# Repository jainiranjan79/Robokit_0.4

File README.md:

# scratchduino-RoboKit v0.4
This repository includes **body, schematics, PCB, documentation and sources** for RoboKit v0.4

#Directories
* Body - *the body of roboplatform and sensors*
* Documentation - *the .pdf schematics, etc*
* Firmware - *the firmware for RoboKit v0.4*
* PCB - *Printed Circuit Boards for Roboplatform and sensors*
    * Gerber - *gerber files + gerber drill files*
        * Cartridge
        * ...
    * SVG - *svg files without drill files*
        * Cartridge
        * ...
* Sources - *the sources for PCB and Body*
    * Cartridge - *Kicad files for PCB*
        * make - *This bash script distribute Gerber, SVG and PDF files to directories PCB,Documentation*
        * PCB - *Here you need print PCB in svg and gerber formats( read make )*
    * ...

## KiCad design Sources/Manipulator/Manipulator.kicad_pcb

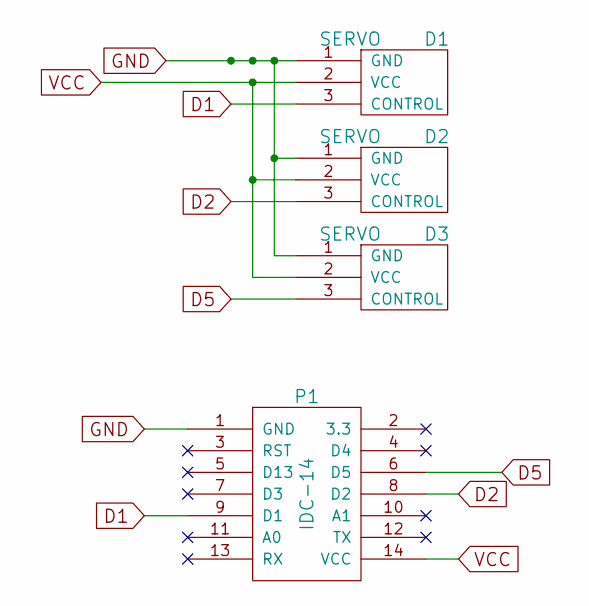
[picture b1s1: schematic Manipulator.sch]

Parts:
D1, D2, D3: SERVO
P1: IDC-14

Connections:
D1: D1.3 (CONTROL), P1.9 (D1)
D2: D2.3 (CONTROL), P1.8 (D2)
D5: D3.3 (CONTROL), P1.6 (D5)
GND: D1.1 (GND), D2.1 (GND), D3.1 (GND), P1.1 (GND)
VCC: D1.2 (VCC), D2.2 (VCC), D3.2 (VCC), P1.14 (VCC)

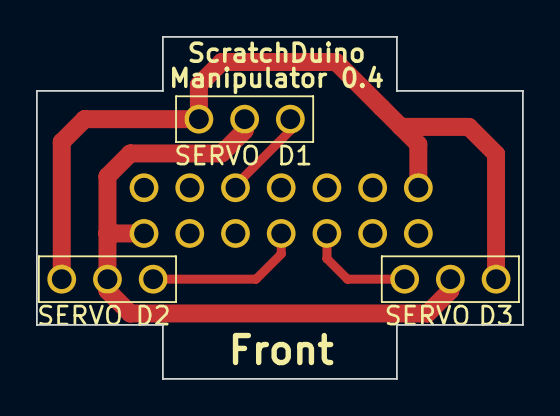
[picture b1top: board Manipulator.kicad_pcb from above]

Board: 2 copper layers, 27.0 x 19.0 mm, 4 parts (1 on the bottom side), 5 nets.

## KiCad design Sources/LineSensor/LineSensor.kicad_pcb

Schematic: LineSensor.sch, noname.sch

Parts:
D1: INFAREDPHOTODIODE
D2: INFAREDLED
P1: SENSOR
R1: 100
R3: 100K

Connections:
unnamed: D1.1, P1.4 (A), R3.1
unnamed: D1.2, P1.2 (VCC), R1.1
unnamed: D2.2, P1.1 (GND), R3.2
unnamed: D2.1, R1.2

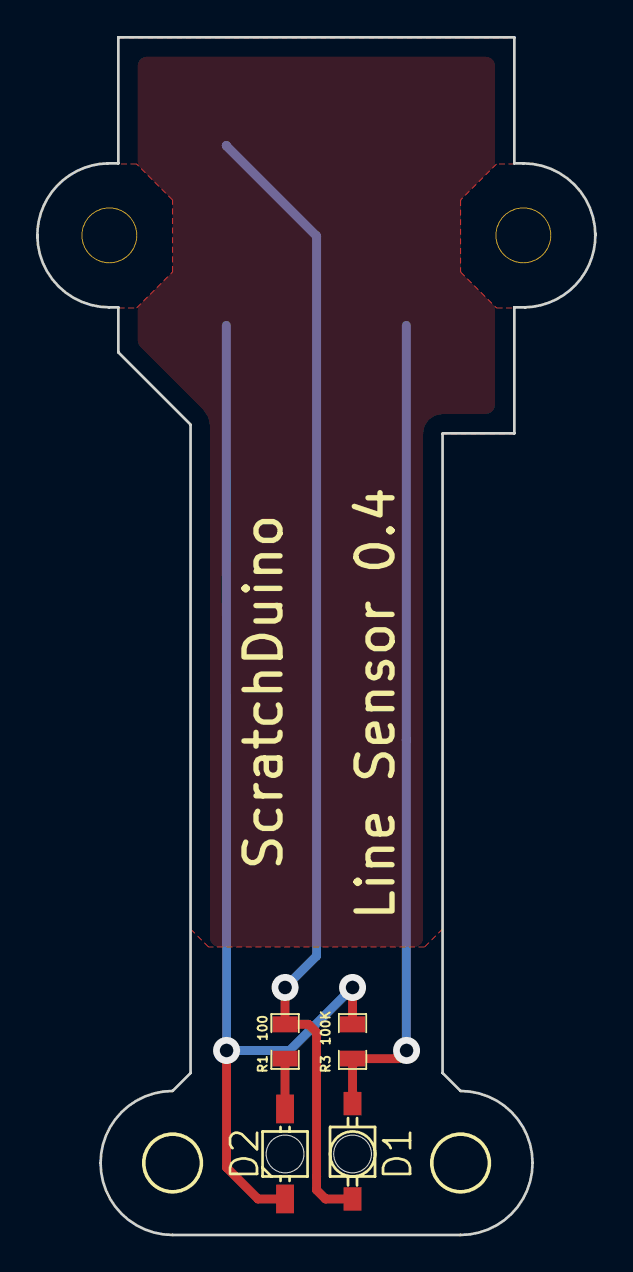
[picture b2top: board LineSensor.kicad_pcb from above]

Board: 2 copper layers, 31.0 x 66.5 mm, 5 parts (1 on the bottom side), 4 nets.

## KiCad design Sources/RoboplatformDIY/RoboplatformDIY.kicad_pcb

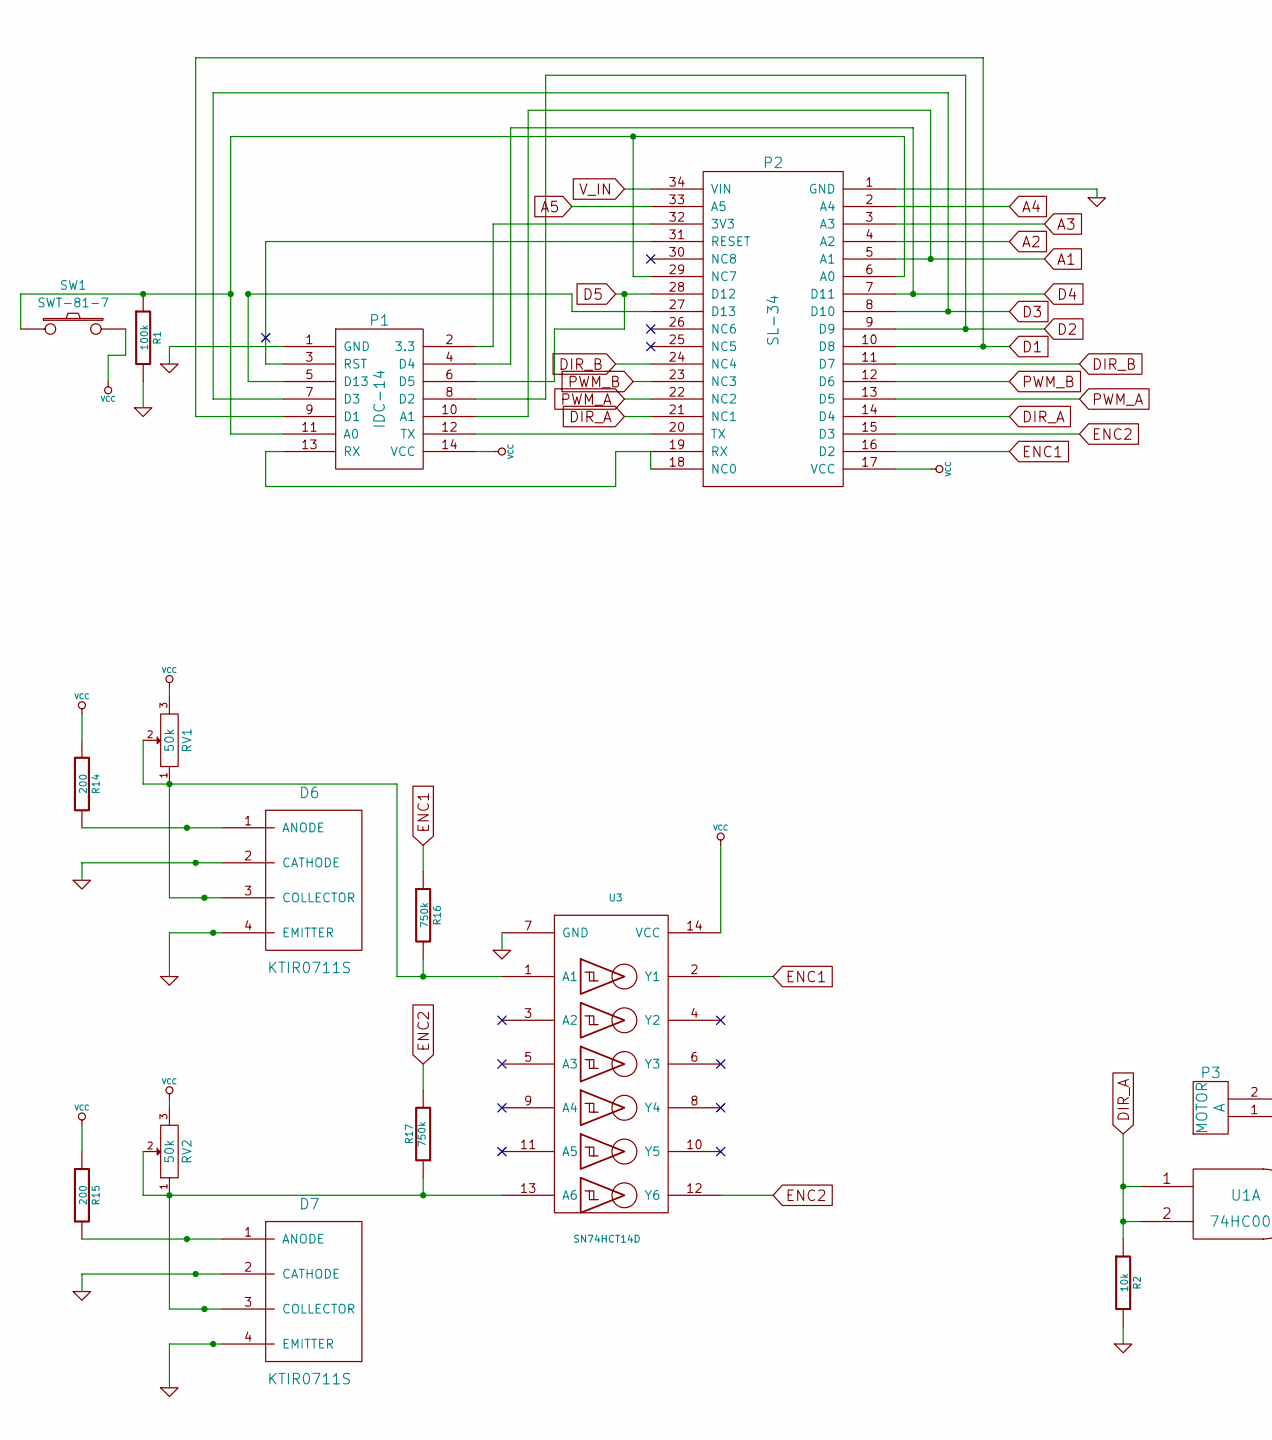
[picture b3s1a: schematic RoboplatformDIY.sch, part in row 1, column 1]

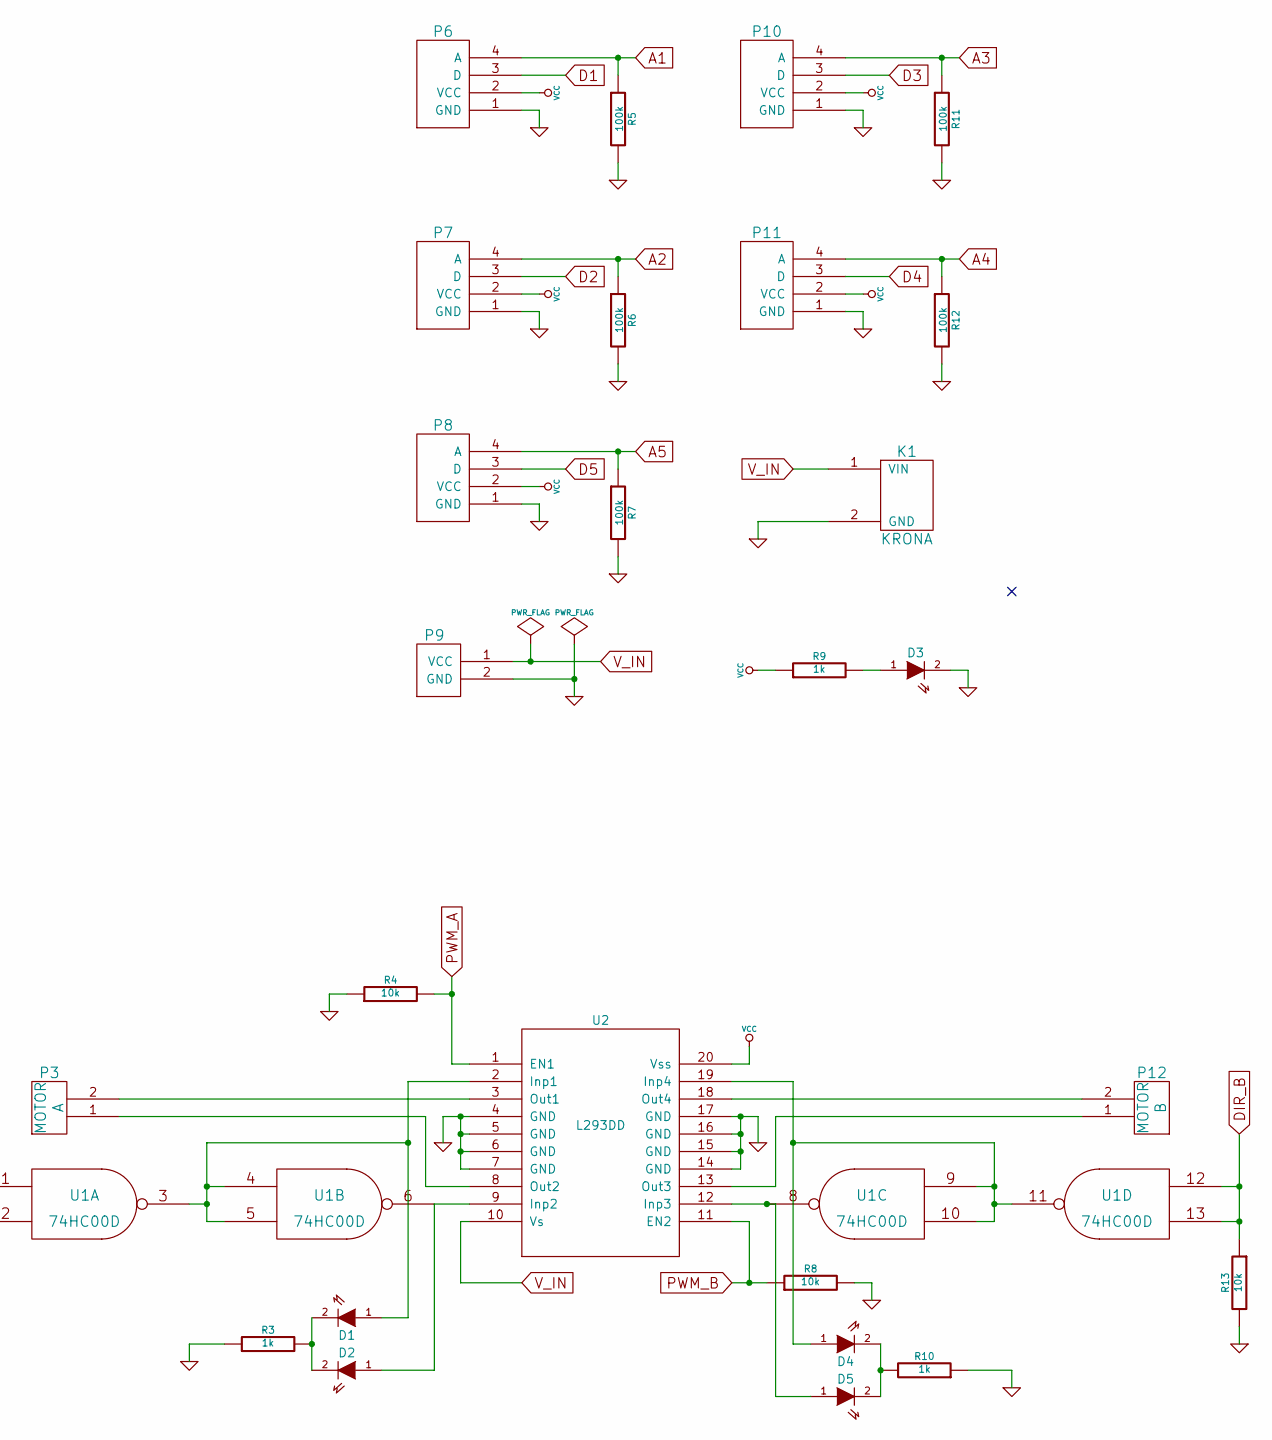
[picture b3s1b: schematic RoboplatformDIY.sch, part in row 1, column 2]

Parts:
D1, D2, D3, D4, D5: LED
D6, D7: KTIR0711S
K1: KRONA
P1: IDC-14
P2: SL-34
P3, P12: MOTOR
P6, P7, P8, P10: SENSOR
P9: POWER
P11: SENSOR
R1, R5, R6, R7, R11, R12: 100k
R2, R4, R8, R13: 10k
R3, R9, R10: 1k
R14, R15: 200
R16, R17: 750k
RV1, RV2: 50k
SW1: SWT-81-7
U1: 74HC00D
U2: L293DD; MODULE
U3: SN74HCT14D

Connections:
A1: P1.10 (A1), P2.5 (A1), P6.4 (A), R5.1
A2: P2.4 (A2), P7.4 (A), R6.1
A3: P2.3 (A3), P10.4 (A), R11.1
A4: P2.2 (A4), P11.4 (A), R12.1
A5: P2.33 (A5), P8.4 (A), R7.1
D1: P1.9 (D1), P2.10 (D8), P6.3 (D)
D2: P1.8 (D2), P2.9 (D9), P7.3 (D)
D3: P1.7 (D3), P2.8 (D10), P10.3 (D)
D4: P1.4 (D4), P2.7 (D11), P11.3 (D)
D5: P1.6 (D5), P2.28 (D12), P8.3 (D)
DIR_A: P2.14 (D4), P2.21 (NC1), R2.1, U1.1, U1.2
DIR_B: P2.11 (D7), P2.24 (NC4), R13.1, U1.12, U1.13
ENC1: P2.16 (D2), R16.1, U3.2 (Y1)
ENC2: P2.15 (D3), R17.2, U3.12 (Y6)
GND: D3.2 (K), D6.2 (CATHODE), D6.4 (EMITTER), D7.2 (CATHODE), D7.4 (EMITTER), K1.2 (GND), P1.1 (GND), P2.1 (GND), P6.1 (GND), P7.1 (GND), P8.1 (GND), P9.2 (GND), P10.1 (GND), P11.1 (GND), R1.2, R2.2, R3.1, R4.1, R5.2, R6.2, R7.2, R8.2, R10.1, R11.2, R12.2, R13.2, U1.7 (GND), U2.4 (GND), U2.5 (GND), U2.6 (GND), U2.7 (GND), U2.14 (GND), U2.15 (GND), U2.16 (GND), U2.17 (GND), U3.7 (GND)
unnamed: P1.12 (TX), P2.20 (TX)
unnamed: P1.13 (RX), P2.18 (NC0), P2.19 (RX)
unnamed: P1.3 (RST), P2.31 (RESET)
unnamed: P1.2 (3.3), P2.32 (3V3)
unnamed: P3.2, U2.3 (Out1)
unnamed: P1.11 (A0), P2.6 (A0), P2.29 (NC7), R1.1, SW1.1
unnamed: P3.1, U2.8 (Out2)
unnamed: D1.1 (A), U1.3, U1.4, U1.5, U2.2 (Inp1)
unnamed: P12.1, U2.13 (Out3)
unnamed: P12.2, U2.18 (Out4)
unnamed: D4.1 (A), U1.9, U1.10, U1.11, U2.19 (Inp4)
unnamed: D7.1 (ANODE), R15.2
unnamed: D6.1 (ANODE), R14.2
unnamed: D2.1 (A), U1.6, U2.9 (Inp2)
unnamed: P1.5 (D13), P2.27 (D13)
unnamed: D3.1 (A), R9.2
unnamed: D7.3 (COLLECTOR), R17.1, RV2.1, RV2.2, U3.13 (A6)
unnamed: D6.3 (COLLECTOR), R16.2, RV1.1, RV1.2, U3.1 (A1)
unnamed: D1.2 (K), D2.2 (K), R3.2
unnamed: D4.2 (K), D5.2 (K), R10.2
unnamed: D5.1 (A), U1.8, U2.12 (Inp3)
PWM_A: P2.13 (D5), P2.22 (NC2), R4.2, U2.1 (EN1)
PWM_B: P2.12 (D6), P2.23 (NC3), R8.1, U2.11 (EN2)
VCC: P1.14 (VCC), P2.17 (VCC), P6.2 (VCC), P7.2 (VCC), P8.2 (VCC), P10.2 (VCC), P11.2 (VCC), R9.1, R14.1, R15.1, RV1.3, RV2.3, SW1.2, U1.14 (VCC), U2.20 (Vss), U3.14 (VCC)
V_IN: K1.1 (VIN), P2.34 (VIN), P9.1 (VCC), U2.10 (Vs)

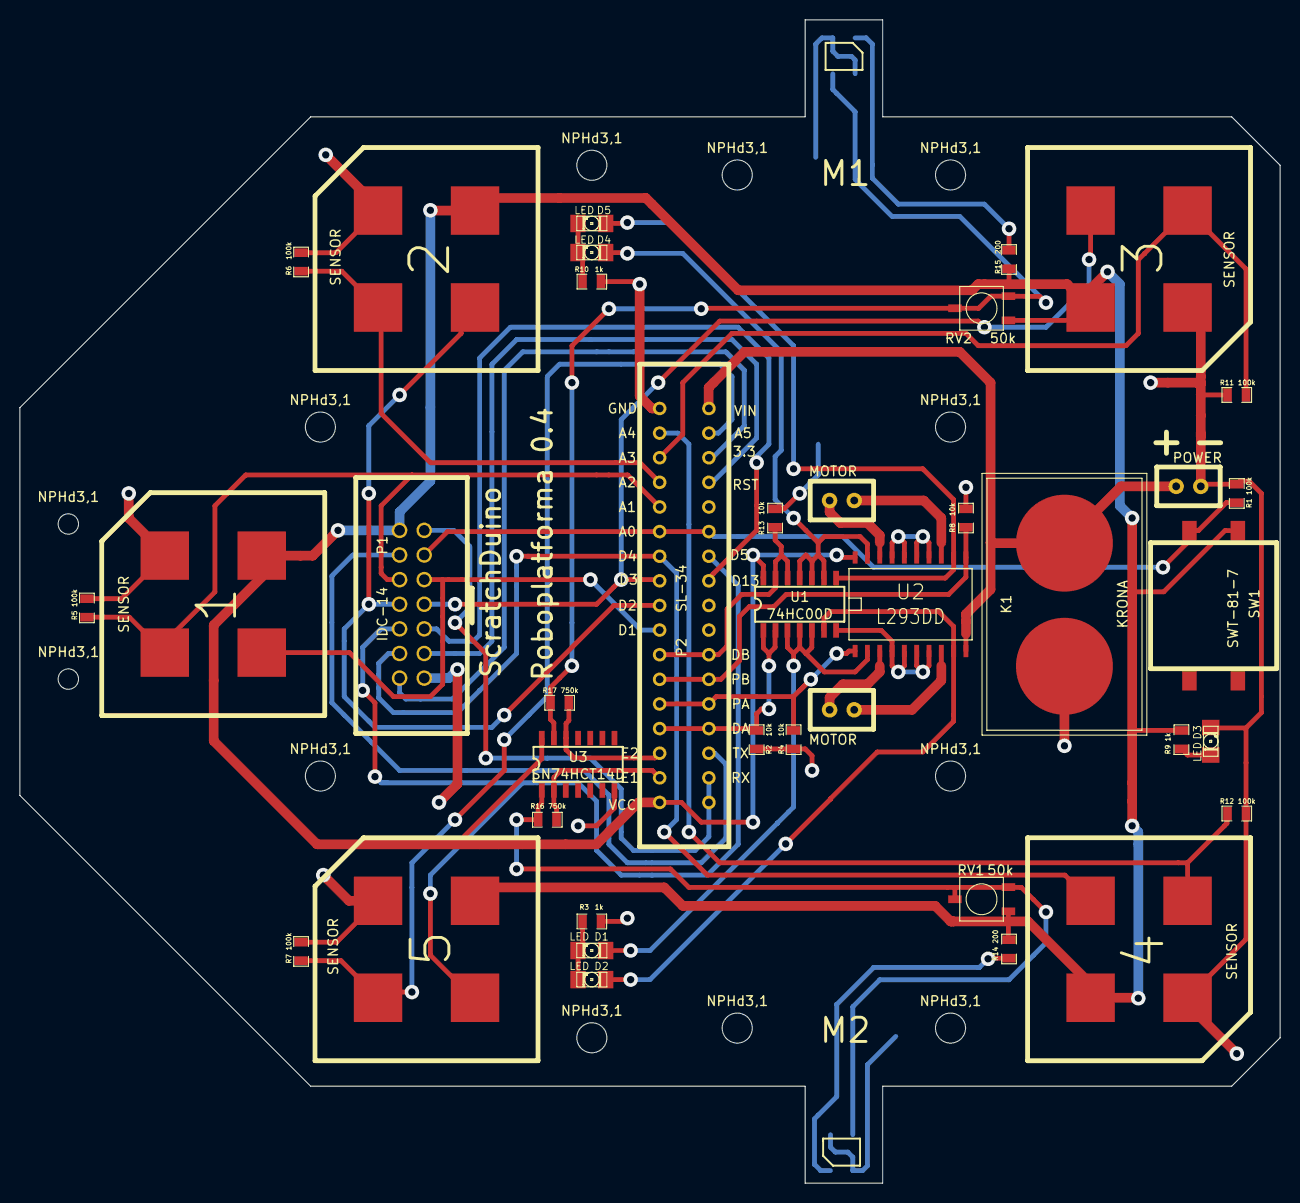
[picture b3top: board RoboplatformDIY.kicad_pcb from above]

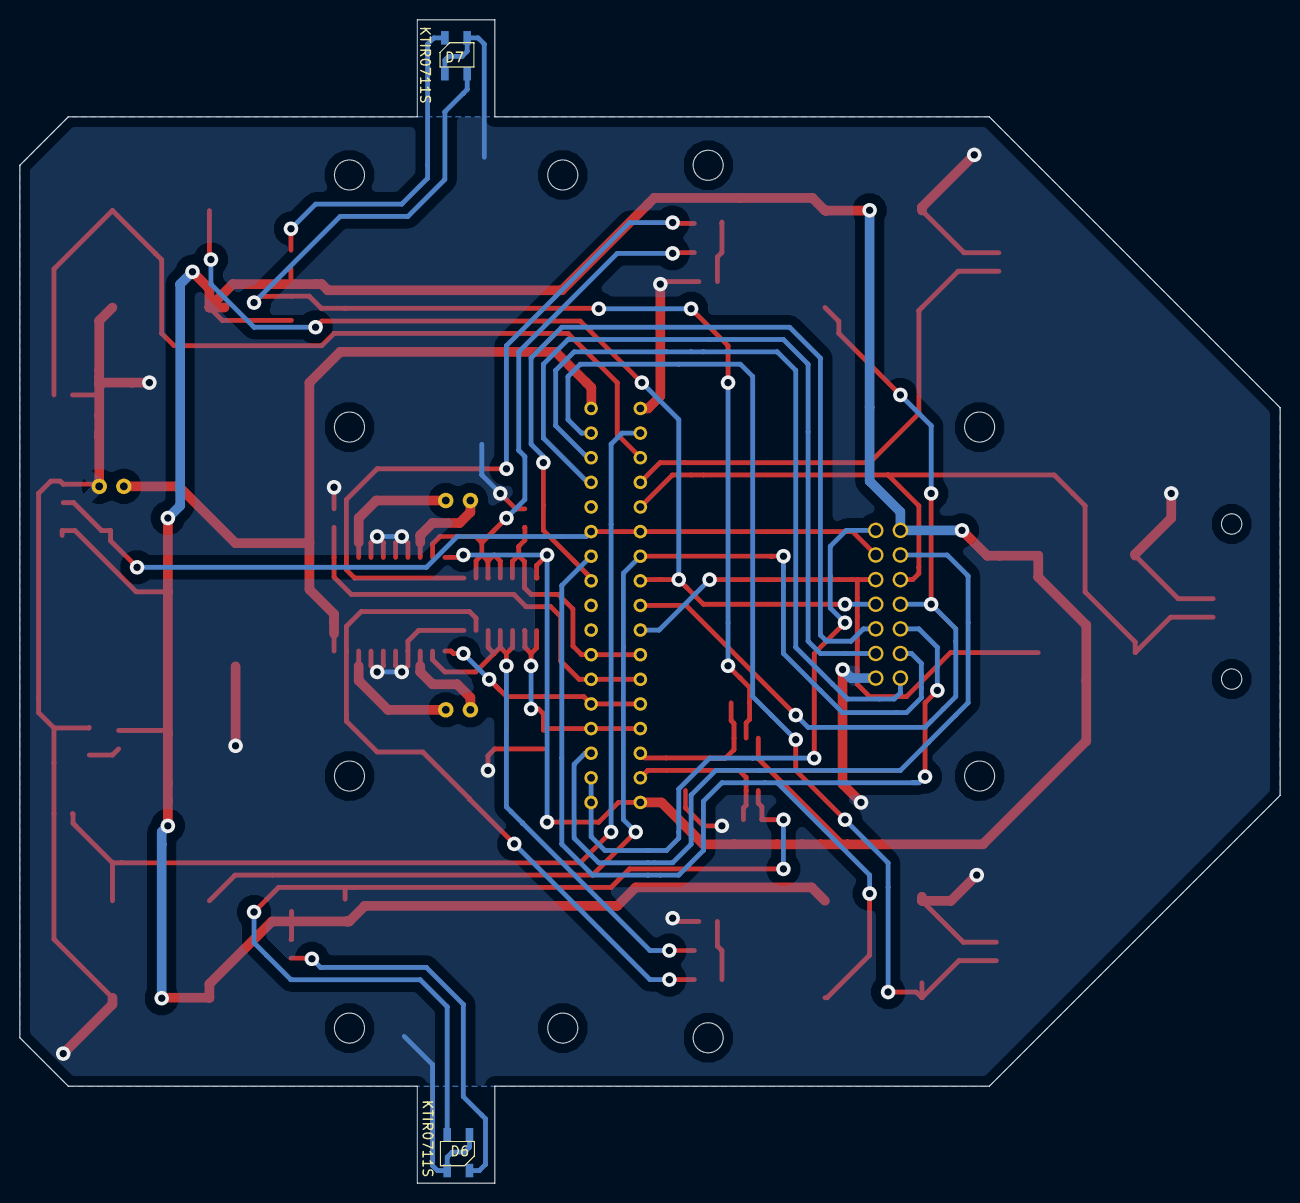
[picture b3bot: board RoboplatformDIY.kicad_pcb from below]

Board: 2 copper layers, 130.0 x 120.0 mm, 53 parts (2 on the bottom side), 40 nets.

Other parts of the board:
NPHd3,1, NPHd3,1#2, NPHd3,1#3, NPHd3,1#4, NPHd3,1#5, NPHd3,1#6, NPHd3,1#7, NPHd3,1#8, NPHd3,1#9, NPHd3,1#10: NPHd3,1
NPHd3,1#11, NPHd3,1#12: NPHd2,1

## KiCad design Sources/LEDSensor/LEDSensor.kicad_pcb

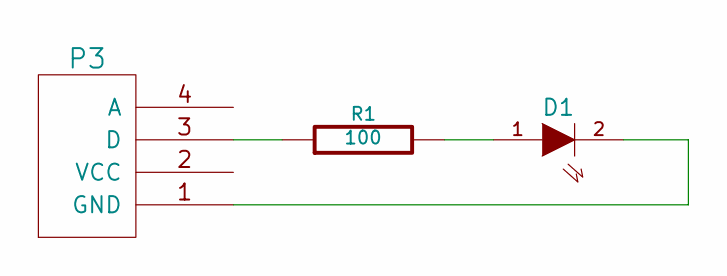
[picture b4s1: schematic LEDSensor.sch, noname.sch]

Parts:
D1: LED
P3: SENSOR
R1: 100

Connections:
unnamed: P3.3 (D), R1.1
unnamed: D1.1 (A), R1.2
unnamed: D1.2 (K), P3.1 (GND)

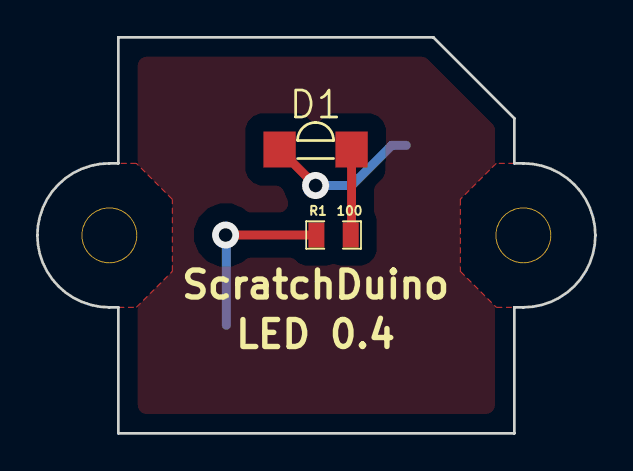
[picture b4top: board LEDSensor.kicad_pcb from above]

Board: 2 copper layers, 31.0 x 22.0 mm, 3 parts (1 on the bottom side), 3 nets.

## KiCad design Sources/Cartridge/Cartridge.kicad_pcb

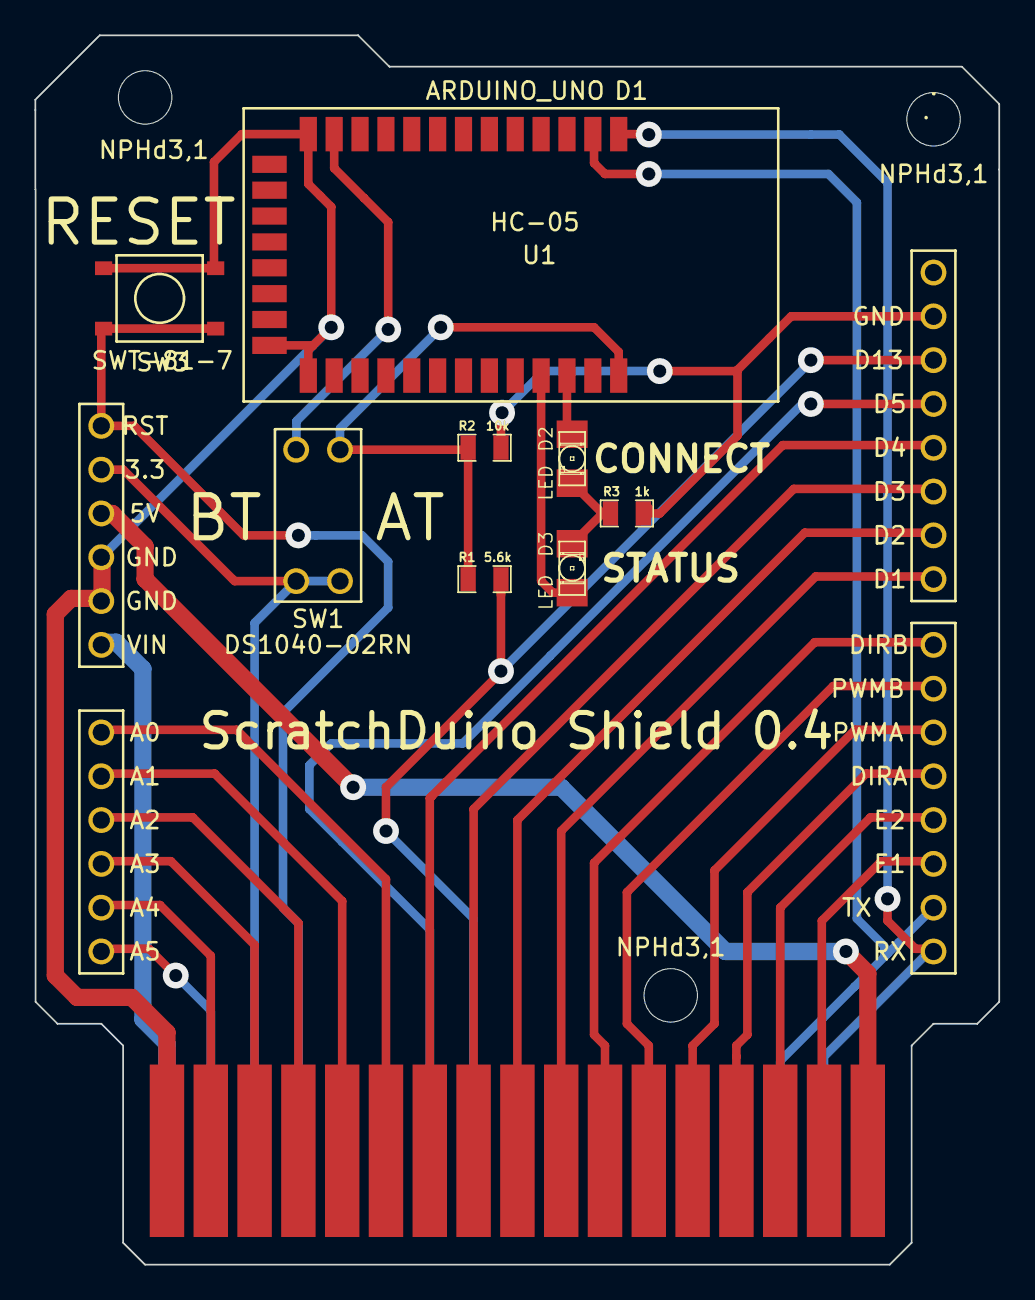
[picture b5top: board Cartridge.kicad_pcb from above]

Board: 2 copper layers, 55.9 x 71.3 mm, 13 parts (1 on the bottom side), 30 nets.

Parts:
D1: ARDUINO_UNO; ARDUINO_SHIELD
D2, D3: LED; LED-1206
NPHd3,1, NPHd3,1#2, NPHd3,1#3: NPHd3,1
P1: SL-34; SL-34_CARTRIDGE
R1: 5.6k; SMD0805
R2: 10k; SMD0805
R3: 1k; SMD0805
SW1: DS1040-02RN
SW3: SWT-81-7; RSTBUTTON
U1: HC-05

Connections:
3.3: D1.27, P1.32, SW1.1, SW1.3
AT: D1.14, P1.27, R1.2
ATDS: R1.1, R2.1, SW1.4, U1.34
GND: D1.15, D1.24, D1.25, P1.1, R2.2, R3.2, SW3.2, U1.13, U1.21, U1.22
unnamed: D1.17, P1.33
unnamed: D1.28, P1.31, SW3.1
unnamed: D1.3, P1.16
unnamed: D1.4, P1.15
unnamed: D1.5, P1.14
unnamed: D1.26, P1.17
unnamed: D1.23, P1.34
unnamed: D1.21, P1.5
unnamed: D1.11, P1.8
unnamed: D1.10, P1.9
unnamed: D1.9, P1.10
unnamed: D1.22, P1.6
unnamed: D1.12, P1.7
unnamed: D1.20, P1.4
unnamed: D1.19, P1.3
unnamed: D1.18, P1.2
unnamed: D1.13, P1.28
unnamed: D1.8, P1.11
unnamed: D1.7, P1.12
unnamed: D1.6, P1.13
unnamed: D2.2, D3.2, R3.1
unnamed: D3.1, U1.31
unnamed: SW1.2, U1.12
unnamed: D2.1, U1.32
RX: D1.1, P1.19, U1.1
TX: D1.2, P1.20, U1.2

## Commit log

2015-10-27 PCB and sources
2015-11-03 Body has been added
2015-11-03 new IR Distance Sensor
2016-01-28 todo and changelog added
2016-01-28 todo updated
